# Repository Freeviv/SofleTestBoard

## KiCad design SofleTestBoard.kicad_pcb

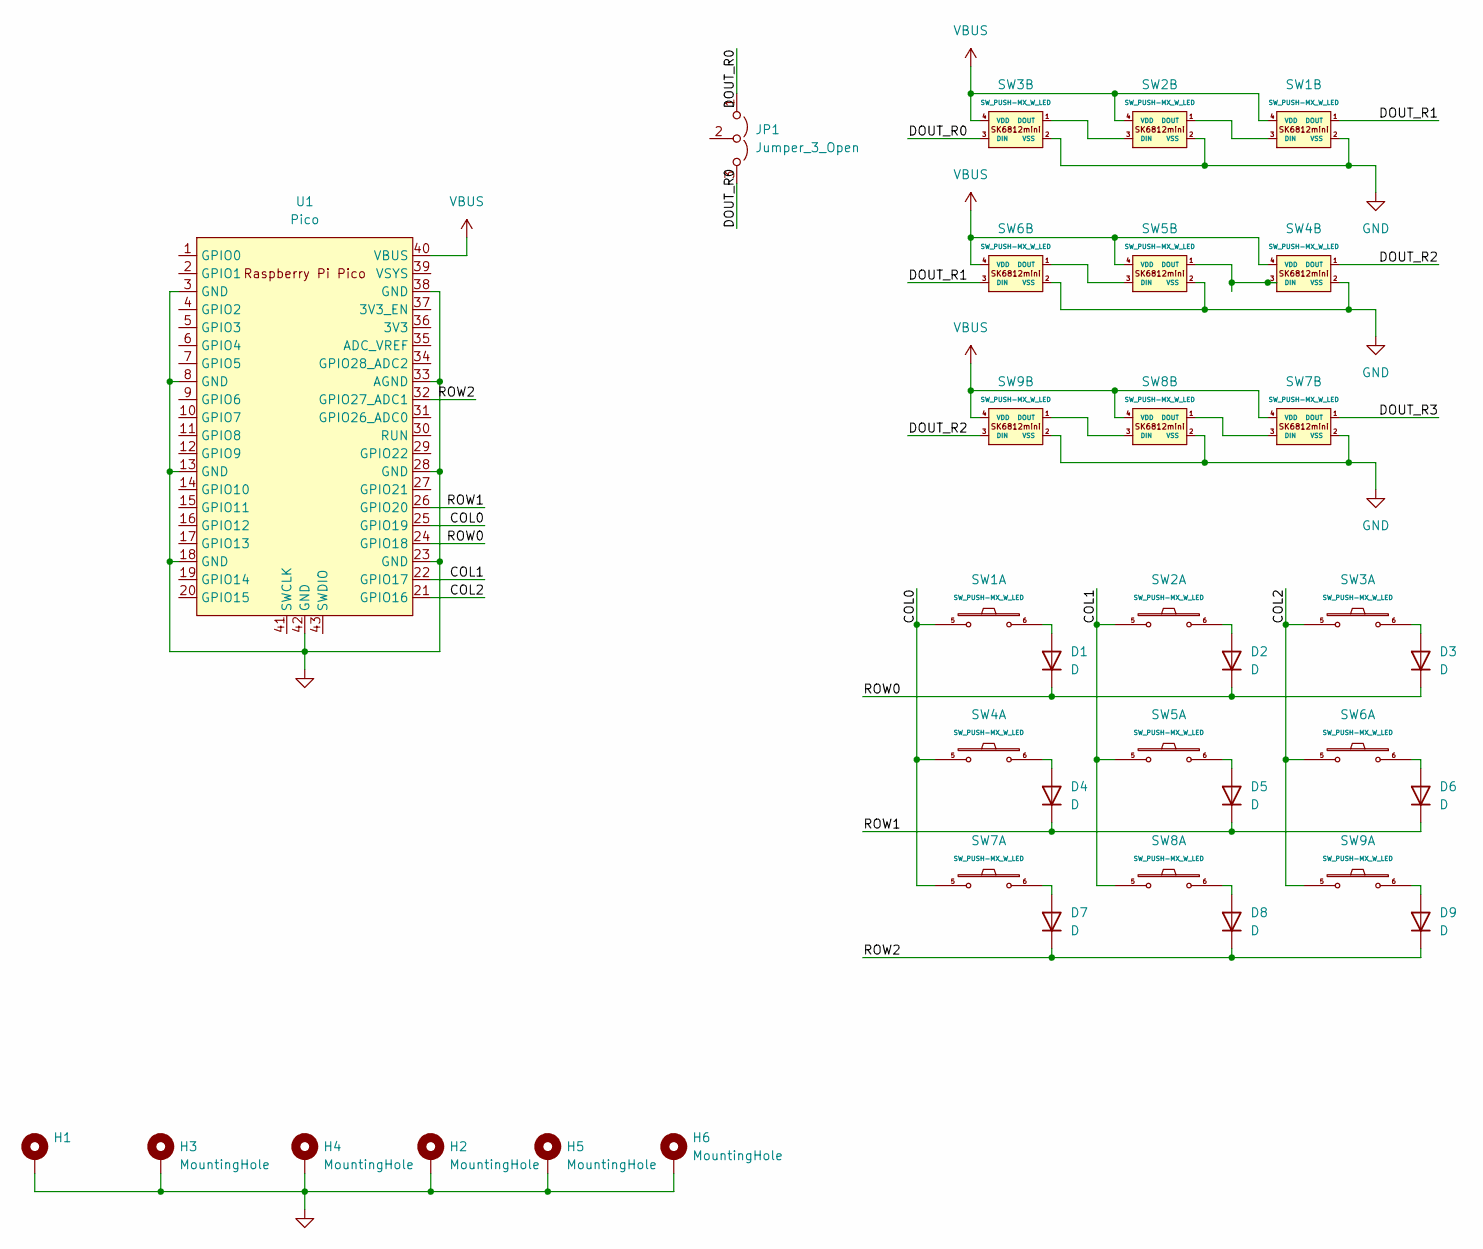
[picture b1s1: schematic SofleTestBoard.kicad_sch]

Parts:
D1, D2, D3, D4, D5, D6, D7, D8, D9: D; D_SOD-123_Dual
H1: (no value)
H2, H3, H4, H5: MountingHole
H6: MountingHole; MountingHole_2.5mm_Pad_TopBottom
JP1: Jumper_3_Open; SolderJumper-3_P1.3mm_Open_RoundedPad1.0x1.5mm_NumberLabels
SW1, SW2, SW3, SW4, SW5, SW6, SW7, SW8, SW9: SW_PUSH-MX_W_LED; 5050_and_cherry
U1: Pico; RPi_Pico_SMD_SMD

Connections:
/COL0: SW1.5, SW4.5, SW7.5, U1.25 (GPIO19)
/COL1: SW2.5, SW5.5, SW8.5, U1.22 (GPIO17)
/COL2: SW3.5, SW6.5, SW9.5, U1.21 (GPIO16)
/DOUT_R0: JP1.1 (A), JP1.3 (B), SW3.3 (DIN)
/DOUT_R1: SW1.1 (DOUT), SW6.3 (DIN)
/DOUT_R2: SW4.1 (DOUT), SW9.3 (DIN)
/DOUT_R3: SW7.1 (DOUT)
/ROW0: D1.1 (K), D2.1 (K), D3.1 (K), U1.24 (GPIO18)
/ROW1: D4.1 (K), D5.1 (K), D6.1 (K), U1.26 (GPIO20)
/ROW2: D7.1 (K), D8.1 (K), D9.1 (K), U1.32 (GPIO27_ADC1)
unnamed: D1.2 (A), SW1.6
unnamed: D2.2 (A), SW2.6
unnamed: D3.2 (A), SW3.6
unnamed: D4.2 (A), SW4.6
unnamed: D5.2 (A), SW5.6
unnamed: D6.2 (A), SW6.6
unnamed: D7.2 (A), SW7.6
unnamed: D8.2 (A), SW8.6
unnamed: D9.2 (A), SW9.6
unnamed: SW1.3 (DIN), SW2.1 (DOUT)
unnamed: SW2.3 (DIN), SW3.1 (DOUT)
unnamed: SW4.3 (DIN), SW5.1 (DOUT)
unnamed: SW5.3 (DIN), SW6.1 (DOUT)
unnamed: SW7.3 (DIN), SW8.1 (DOUT)
unnamed: SW8.3 (DIN), SW9.1 (DOUT)
VBUS: SW1.4 (VDD), SW2.4 (VDD), SW3.4 (VDD), SW4.4 (VDD), SW5.4 (VDD), SW6.4 (VDD), SW7.4 (VDD), SW8.4 (VDD), SW9.4 (VDD), U1.40 (VBUS)

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
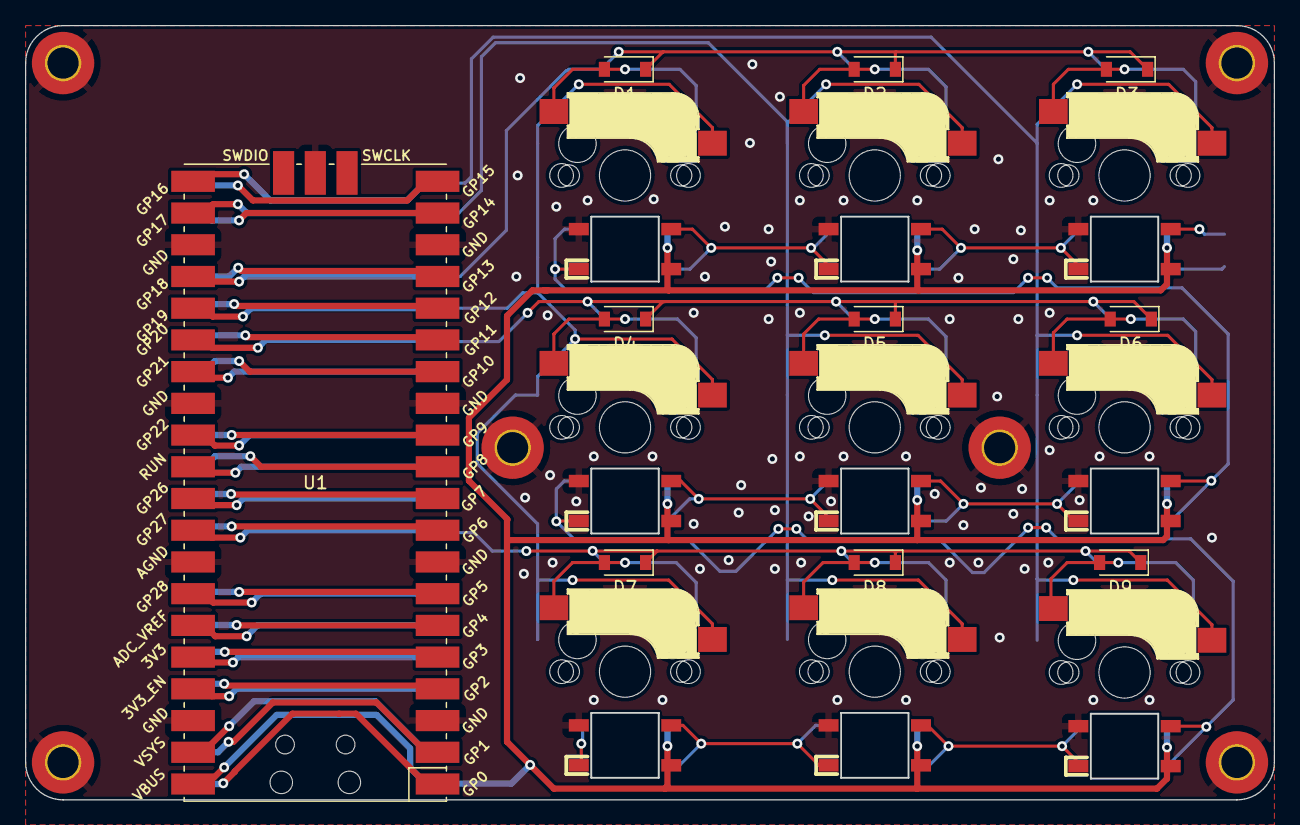
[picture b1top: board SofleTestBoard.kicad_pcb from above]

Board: 2 copper layers, 100.0 x 61.9 mm, 26 parts (1 on the bottom side), 26 nets.

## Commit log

2022-10-28 init commit
2022-10-28 PoC. MCU neets to be rotated
2022-10-29 Fixed backup ignore
2022-10-29 Finished initial design. No DRC run yet
2022-10-29 DRC setup and executed
2022-10-29 Generated Gerbers for JLCPCB
